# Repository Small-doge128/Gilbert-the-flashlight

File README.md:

# About
A really nice flashlight, which is small as a box of TIC-TACs with two buttons, an OLED and a bright LED powered by a battery. It looks like a samsung SSD and It's my first time using and coding a display. [onshape](https://cad.onshape.com/documents/cd0ef959b6cca3fa70459174/w/619a7eb4bf14ab27515c2c02/e/2342898b3dd9987e8f05f571).

# features
A really nice OLED for informations powered by a 1 200 mAh LiPo battery. The brain is a seeed studio xiao esp32-s3. The main things are the powerfull warm LEDs with a resistor.

# step by step tutorial for firmware

1 - download the whole file called - gilbert the flashlight .bin files.                                                                                              
2 - connect your seeed studio via usb-c.                                                                                                                    
3 - Put it into bootloader mode (hold the **B** button, while holding press the **RST** button and then release).                                                  
4 - open this link in browser -> [esspresif bootloader](https://esptool.spacehuhn.com) (safari won't work install another browser).                                                        
5 - select your port where you have the seeed studio connected.                                                                                  
6 - set the baud rate to **115200**.                                                                                                                    
7 - load the files you downloaded earlier at these memory ofsets.                                                                        
 - `bootloader.bin` -> `0x0`                                                                                                                           
 - `partitions.bin` -> `0x8000`                                                                                                                           
 - `firmware.bin`   -> `0x10000`
                                                                                                        
8 - click **Program** to flash now it should work **enjoy**.

# dimensions
the LED pcb- 38 mm x 8 mm x 1.6 mm                                                                                                                                               
the whole flashlight- 40 mm x 78 mm x 9 mm

# why did i create it
I already had a good flashlight, but this is better and It's more like me with a warmer LEDs which are better and a display that shows lumens and more.

# pictures

| Name | Purpose | Qty | Price (USD) | Distributor | Link |
| --- | --- | --- | --- | --- | --- |
| Gilbert PCB | Connecting the LEDs + heat dissipation | 5 | $4.20 | JLCPCB | [Link](https://jlcpcb.com) |
| seeed studio xiao esp32-s3 | the brain | 1 | $9.26 | AliExpress | [Link](https://www.aliexpress.com/item/1005007341749305.html) |
| LiPo battery 1 200mAh | powering the parts | 1 | $9.55 | AliExpress | [Link](https://www.aliexpress.com/item/1005007000725960.html) |
| AMC7135 LED chip | LED chip for the LEDs | 1 | $0.91 | AliExpress | [Link](https://www.aliexpress.com/item/1005006788149432.html) |
| LEDs nichia 519A 3 500k | for the lighting | 2 | $17.86 | AliExpress | [Link](https://www.aliexpress.com/item/1005004368329867.html) |
| momentary switch | for buttons | 2 | $0.46 | AliExpress | [Link](https://www.aliexpress.com/item/1005003015037539.html) |
| OLED display | for data of the flashlight | 1 | $2.61 | AliExpress | [Link](https://www.aliexpress.com/item/1005008918700196.html) |
| **TOTAL** | | | **$44.85** | | |
| **TOTAL (with tax & shipping)** | | | **$55.00** | | |

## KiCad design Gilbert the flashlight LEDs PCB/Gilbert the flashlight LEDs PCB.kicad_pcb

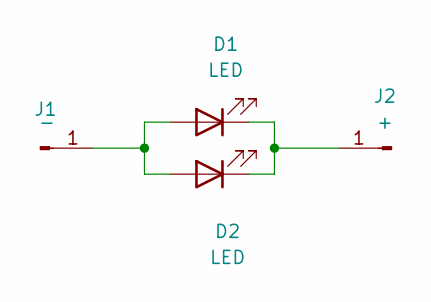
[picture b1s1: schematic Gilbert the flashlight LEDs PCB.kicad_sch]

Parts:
D1, D2: LED; LED_SK6812MINI_PLCC4_3.5x3.5mm_P1.75mm
J1: -; TestPoint_Pad_2.0x2.0mm
J2: +; TestPoint_Pad_2.0x2.0mm

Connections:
unnamed: D1.2 (A), D2.2 (A), J1.1 (Pin_1_1)
unnamed: D1.1 (K), D2.1 (K), J2.1 (Pin_1_1)

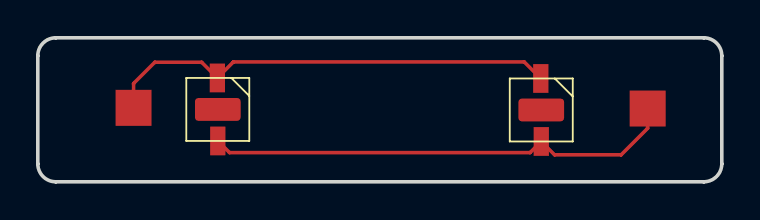
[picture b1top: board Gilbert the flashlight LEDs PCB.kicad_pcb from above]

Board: 2 copper layers, 38.0 x 8.0 mm, 4 parts (0 on the bottom side), 2 nets.
